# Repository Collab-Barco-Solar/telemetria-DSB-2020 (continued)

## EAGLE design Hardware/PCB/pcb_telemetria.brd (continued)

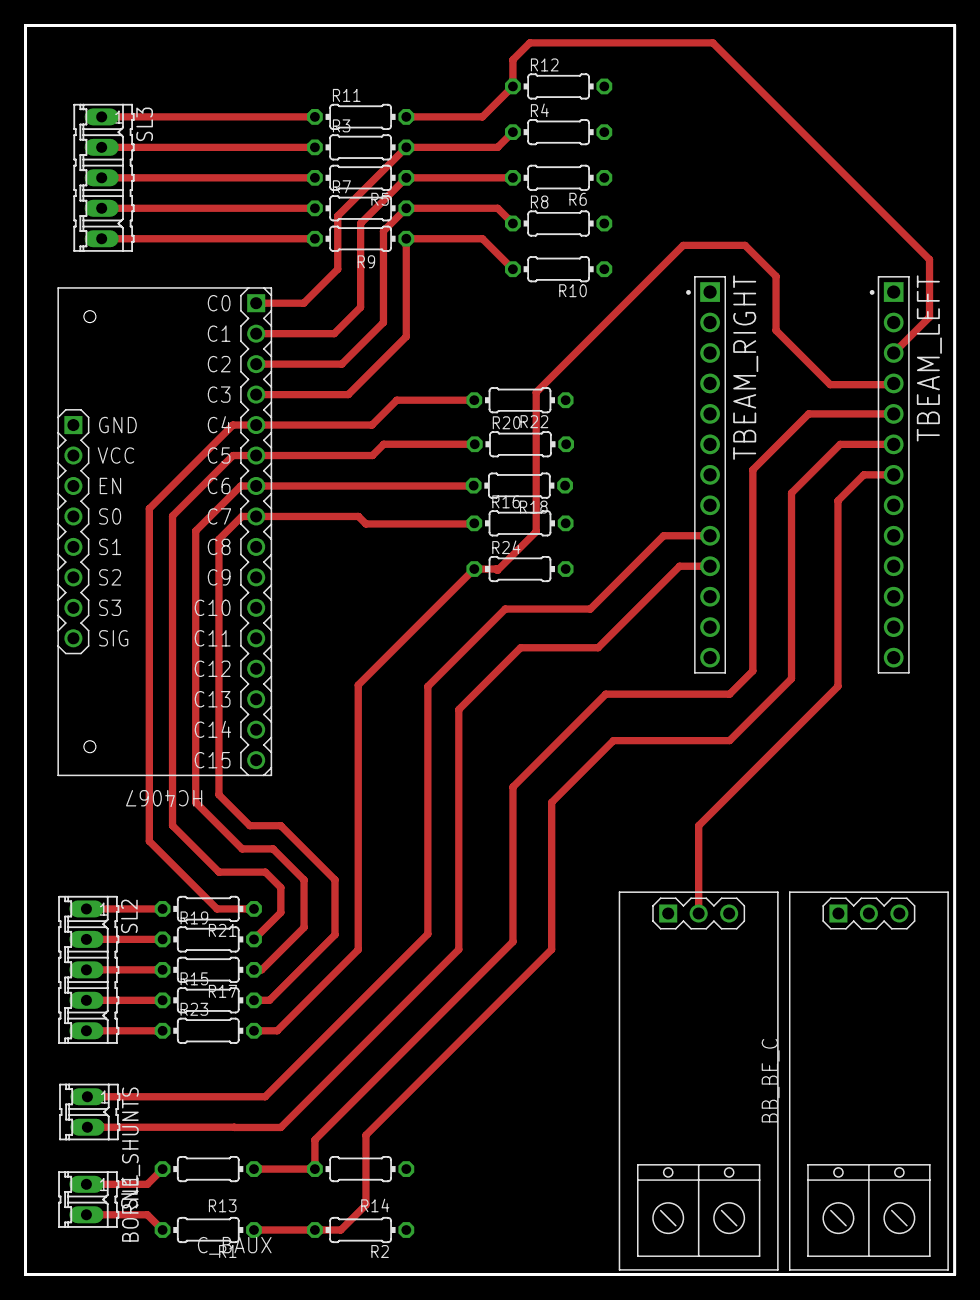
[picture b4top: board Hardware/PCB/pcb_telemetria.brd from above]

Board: 2 copper layers, 77.5 x 104.1 mm, 33 parts (0 on the bottom side), 29 nets.

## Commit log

2019-03-25 Uploaded the old code from 2018
    This code was a version close to what was used on the previous race
2019-04-21 Added first transmission prototype, shows signal and packet via Serial
2019-04-25 Wrote on README
2019-04-25 Changed the code base to english
2019-05-03 Added analog measure file and modified some stuff in the sender
2019-05-04 Git test
2019-05-20 Removed duplicate folder
2019-05-20 added info on the README
2019-05-20 Added a pontentiometer testing module
2019-05-31 Added GPS module (unfinished)
2019-06-08 Added analog to digital sketch using a ADS1115 board
2019-06-08 Moved ads.ino file
2019-06-08 Testing LoRa parameters
2019-06-11 Added a simpler version of the ADS1115 circuit code. Working
2019-06-13 Tweaked the print
2019-07-05 Tweaking GPS
2019-07-06 Added efficiency tracking, renamed the sender to transmitter and fixed the message for testing purposes
2019-07-06 added a field test code
2019-07-06 Added a CSV format to the Serial receiver output
2019-07-07 Added a distance measuring code
2019-07-22 lamp
2019-07-31 Update photovoltaic.ino
    Atualizacao de um comentario
2019-07-31 Update photovoltaic.ino
    UP
2019-07-31 circuito update
    circuito com medicao das bombas e bateria
2019-08-01 Removed medevoltagem folder and tweaked photovoltaic
2019-08-01 implementacao coolers
2019-08-01 Started basic code for the boat
2019-08-01 Added code with gps
2019-08-01 up_circuit
2019-08-01 up_circuito
2019-08-15 Tweaked the ads
2019-08-16 Updated GPS code and boat test transmitter
2019-08-21 Added readings and functions
2019-09-01 adding telemetria PCB
    not concluded
2019-09-03 update
    adicao de rotas na pcb
2019-09-04 Adicao de Rotas e mudanca de nomes
2019-09-04 ultima ligacao nao GND
2019-09-10 battery_discharge code
    Code for the ads to the battery discharge test.
2019-09-10 valores das resistencias (att)
    update
2019-09-12 log das baterias dados
2019-09-13 Analise do teste de baterias
    Código do teste das baterias finalizado
2019-09-18 up caqui
    aa
2019-09-18 library
2019-09-21 primeira versao placa
2019-09-21 uplix
2019-10-01 Update Guilherme
2019-10-02 Changes in the board and code
    mudancas no codigo e placa
2019-10-02 ultima att
    up
2019-10-02 Simplified the transmitter
2019-10-03 att nos pinos e adicao de regulador pwm
    tired
2019-10-03 Erro no código
    A porta enable estava setada no pino errado (4 e esta é a de signal), mudei para 23. No entanto no código em nenhum momento enable é definida (nem como low nem como high).
2019-10-03 Placa finalizada, aguardando ajustes
    Finalizou-se o roteamento pre testes. Aguardando testes para realização de ajustes.
2019-10-03 Limpeza e mudanca dos nomes
    Update de organizacao
2019-10-04 Added boat receiver code
2019-10-05 updating the code
    Att code to be aligned with the board
2019-10-05 mux test
2019-10-05 organizing
2019-10-05 Cleaned the code
2019-10-05 organizing obsolet
2019-10-05 organizing current folder
2019-10-05 mux_att
2019-10-05 fuck_it
2019-10-06 attualizando
2019-10-07 Att in the rate of resistores (adding DT5_RATIO)
2019-10-09 Schematic e code conforming
    The mux pins in the code are now updated (EN on the ground rsrs) and the circuit project are already routed with the new mux pins
2019-10-09 New libraries
    Some not used eagle libraries
2019-10-09 BUTTON LOGIC FIX
    Updating the logic on the button response.
2019-10-09 Update bibliotecattgo.lbr
    Adding SD CARD
2019-10-09 mudancas na placa
    resistores atualizados com sucesso
2019-10-09 Libraries list
2019-10-10 update
    Delay in muxChannel.. maybe too much. I need to test what is the minimum required for good performance.
2019-10-10 Updates and test code
    fixing the logic number (4096 to 4095)
2019-10-11 changing mux signal port
2019-10-12 Um ads 1115 que presta
2019-10-12 adicionei o ADC interno
2019-10-18 testando adc
2019-10-19 commit dente de serra
2019-10-19 adding tiny gps
2019-10-20 logs ADC reads
    Different kinds of inputs in adc pin.
2019-10-20 adc ajustado
2019-10-20 organizacao
2019-10-20 organizando
2019-10-21 polyfit on transmitter
2019-10-22 correcao_transmitter
2019-10-27 Organazing
    Change some bad names and adding the cell and multiplexed type.
2019-10-27 Better type of variables for potentiometer
    Multiply int by floats causes some inaccurateresults. So, now they are all floats.
2019-11-02 up
    iniciando separacao do mux
2019-11-15 att placa com SD
2019-11-15 consertando e adicionando cartao sd
2019-11-15 removendo lixos
2019-11-15 jlcpcb added
2019-11-15 placa com trilhas finas e Mini-fit molex
2019-11-17 avancos na placa
2019-11-17 iniciando codigo do LCD
2019-11-20 lcd funcionando estranhamente
2019-11-21 adicao de conexao para pinos extras
2019-11-22 LCD testado no transmitter
2019-11-26 Moved some files and deleted thrash
2019-11-26 Added serial comunication modules
2019-11-26 Serial readings
2019-11-27 Added SD card reader
2019-11-27 LCD 1.0
2019-12-14 adding connector to sd card and capacitors
2019-12-14 adding connector to sdcard and ground plane
2019-12-14 Added a data visualization test, working on it
2019-12-16 PCB to print in ERUS
2019-12-26 att pra caqui baixar
    ice crackerr
2019-12-26 veja agora ice
2019-12-26 att blink do lcd
2019-12-26 voltando com a tinyGPS
2019-12-26 Update lcd_code_caqui.ino
    os números estão acordando
2019-12-27 removendo para futuro merge
2019-12-27 update_to_merge
2019-12-27 Arrumando o que o agricio faz 🙊
2019-12-27 removing latest and changing obsolete folder
2019-12-27 Bringing things out from latest
2019-12-27 removing automatic save files
2019-12-27 changes to merge
2019-12-27 removendo "circuit"
2019-12-30 Receiving and writing serial data
2019-12-30 Deleted telemetry folder and moved its contents to boat
2020-01-03 up_no important changes
2020-01-03 gps library
2020-01-06 plaquinha extra pro painel
2020-01-07 placa_painel
2020-01-13 increased of vias diameter
2020-01-26 zip LCD library
2020-01-28 Data viz update
2020-01-28 Added different sync word and code rate
2020-01-28 Added a boat speed variable as boat_speed and removed strings being sent via LoRa
2020-01-28 on changes
    applying LCD features
2020-01-29 Fixed sync word bug
2020-01-29 Mirrored the receiver to the transmitter
2020-01-29 att transmitter
2020-01-29 First day of tests, logs added
2020-01-29 Changed syncword to 2D
2020-01-29 Mudancas nos prints
    Removing some Serial.Print's (even if were just comments)
2020-01-30 Removing cruise from lora package
2020-01-30 Changed log names and script to make it windows friendly
2020-01-30 Adding notes about telemetry tests
2020-01-30 Adding ACS code and removing some
    Useless lora prints removed
2020-01-30 Solving ADS error
2020-01-30 att receiver header and getting back reverse
2020-01-30 Deleted last comma on the CSV header
2020-01-30 Made the receiver more csv friendly
2020-01-30 Fixed the CSV delimiter parameter
2020-01-30 changing infos about prints
2020-01-30 Fixed header printing without \n
2020-01-31 corrections in mux pins defined and list
2020-01-31 Added LCD Alternative Technical Resourse (ATR, for short) arduino code
